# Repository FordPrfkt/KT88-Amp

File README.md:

# KT88-Amp
Tube Amplifier using KT88 Tubes

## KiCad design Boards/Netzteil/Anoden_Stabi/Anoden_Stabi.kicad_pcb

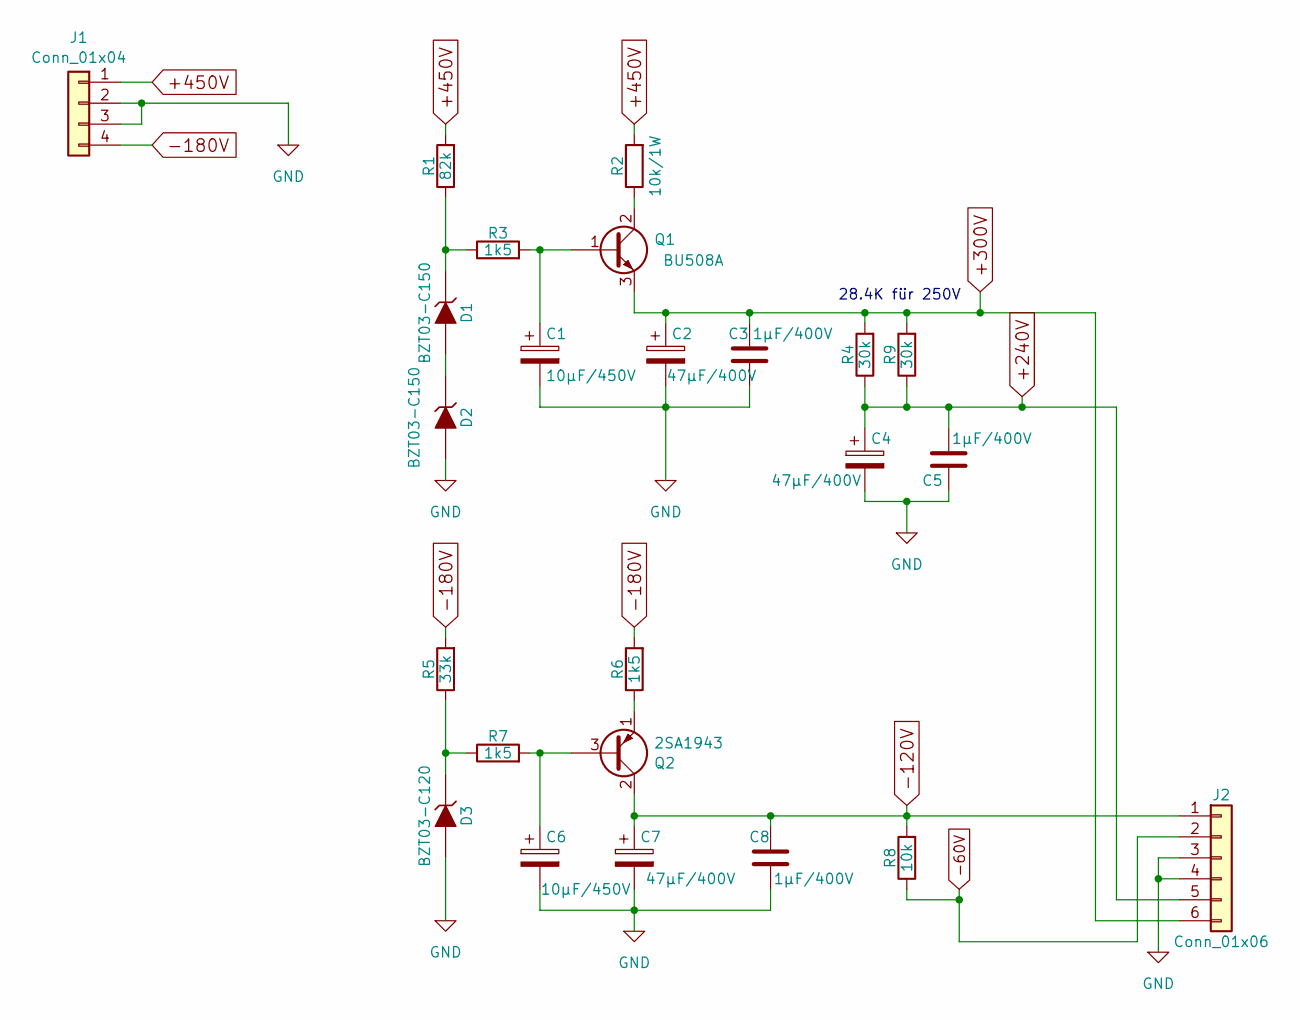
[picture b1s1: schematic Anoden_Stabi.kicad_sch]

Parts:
C1, C6: 10µF/450V; CP_Radial_D12.5mm_P5.00mm
C2, C4, C7: 47µF/400V; CP_Radial_D17.0mm_P7.50mm
C3, C5, C8: 1µF/400V; C_Rect_L31.5mm_W11.0mm_P27.50mm_MKS4
D1, D2: BZT03-C150; D_DO-41_SOD81_P10.16mm_Horizontal
D3: BZT03-C120; D_DO-41_SOD81_P10.16mm_Horizontal
J1: Conn_01x04; Molex_Mini-Fit_Jr_5566-04A_2x02_P4.20mm_Vertical
J2: Conn_01x06; Molex_Mini-Fit_Jr_5566-06A_2x03_P4.20mm_Vertical
Q1: BU508A; TO-3P-3_Vertical
Q2: 2SA1943; TO-3P-3_Vertical
R1: 82k; R_Axial_DIN0207_L6.3mm_D2.5mm_P10.16mm_Horizontal
R2: 10k/1W; R_Axial_DIN0414_L11.9mm_D4.5mm_P15.24mm_Horizontal
R3, R6, R7: 1k5; R_Axial_DIN0414_L11.9mm_D4.5mm_P15.24mm_Horizontal
R4, R9: 30k; R_Axial_DIN0207_L6.3mm_D2.5mm_P10.16mm_Horizontal
R5: 33k; R_Axial_DIN0207_L6.3mm_D2.5mm_P10.16mm_Horizontal
R8: 10k; R_Axial_DIN0414_L11.9mm_D4.5mm_P15.24mm_Horizontal

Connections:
+240V: C4.1, C5.2, J2.5, R4.1, R9.1
+300V: C2.1, C3.2, J2.6, Q1.3 (E), R4.2, R9.2
+450V: J1.1, R1.2, R2.2
-60V: J2.2, R8.1
-120V: C7.1, C8.2, J2.1, Q2.2 (C), R8.2
-180V: J1.4, R5.2, R6.2
GND: C1.2, C2.2, C3.1, C4.2, C5.1, C6.2, C7.2, C8.1, D2.2 (A), D3.2 (A), J1.2, J1.3, J2.3, J2.4
unnamed: D1.2 (A), D2.1 (K)
unnamed: D1.1 (K), R1.1, R3.1
unnamed: D3.1 (K), R5.1, R7.1
unnamed: C1.1, Q1.1 (B), R3.2
unnamed: Q1.2 (C), R2.1
unnamed: C6.1, Q2.3 (B), R7.2
unnamed: Q2.1 (E), R6.1

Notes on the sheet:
28.4K für 250V

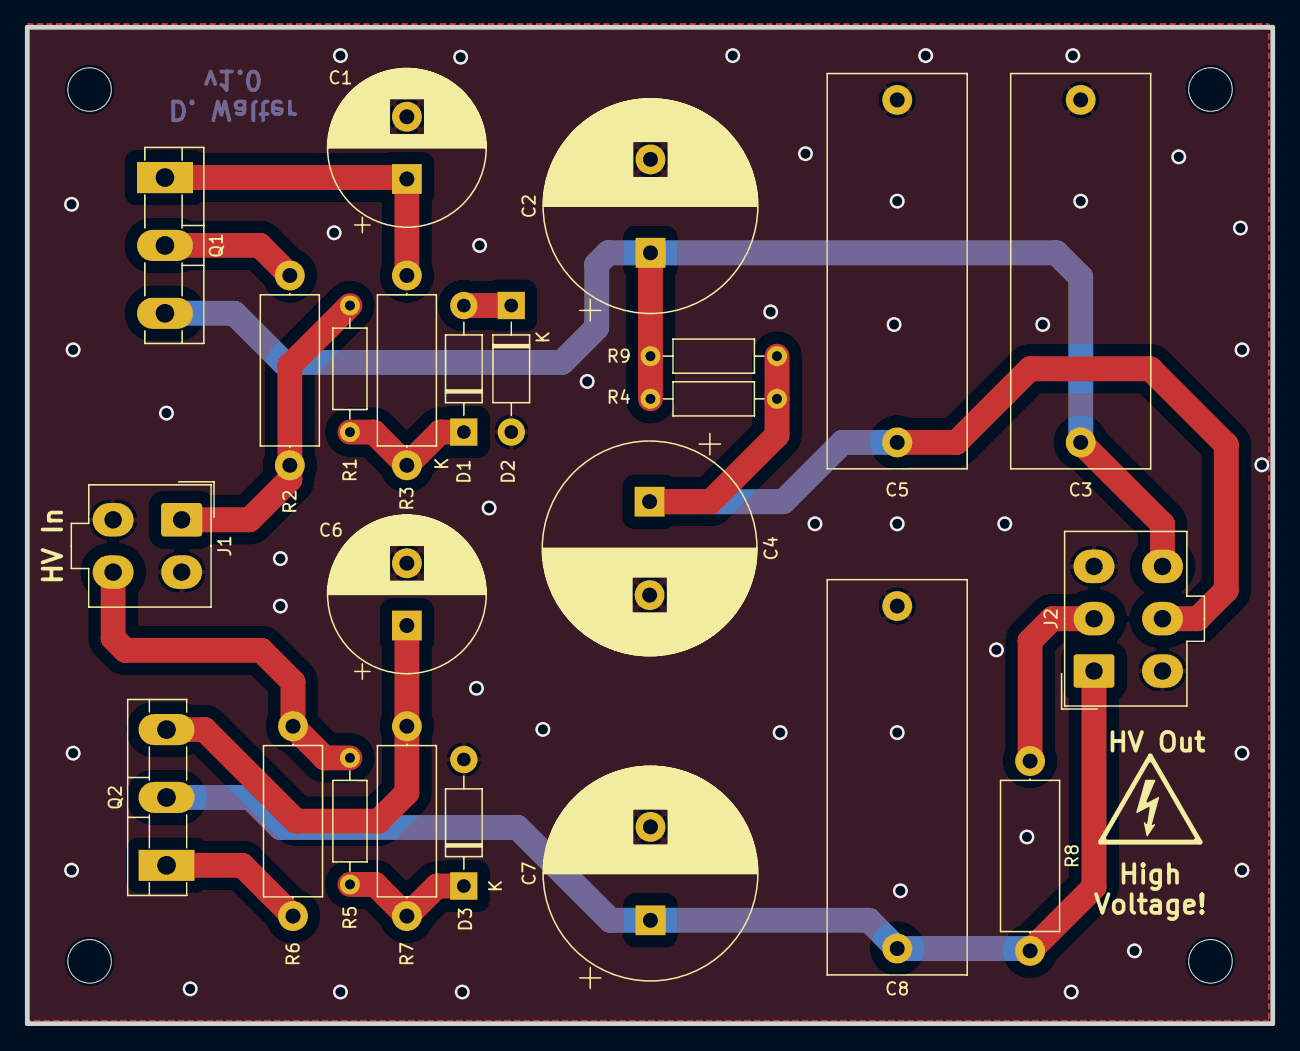
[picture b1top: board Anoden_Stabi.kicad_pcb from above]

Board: 2 copper layers, 100.0 x 80.0 mm, 24 parts (0 on the bottom side), 14 nets.

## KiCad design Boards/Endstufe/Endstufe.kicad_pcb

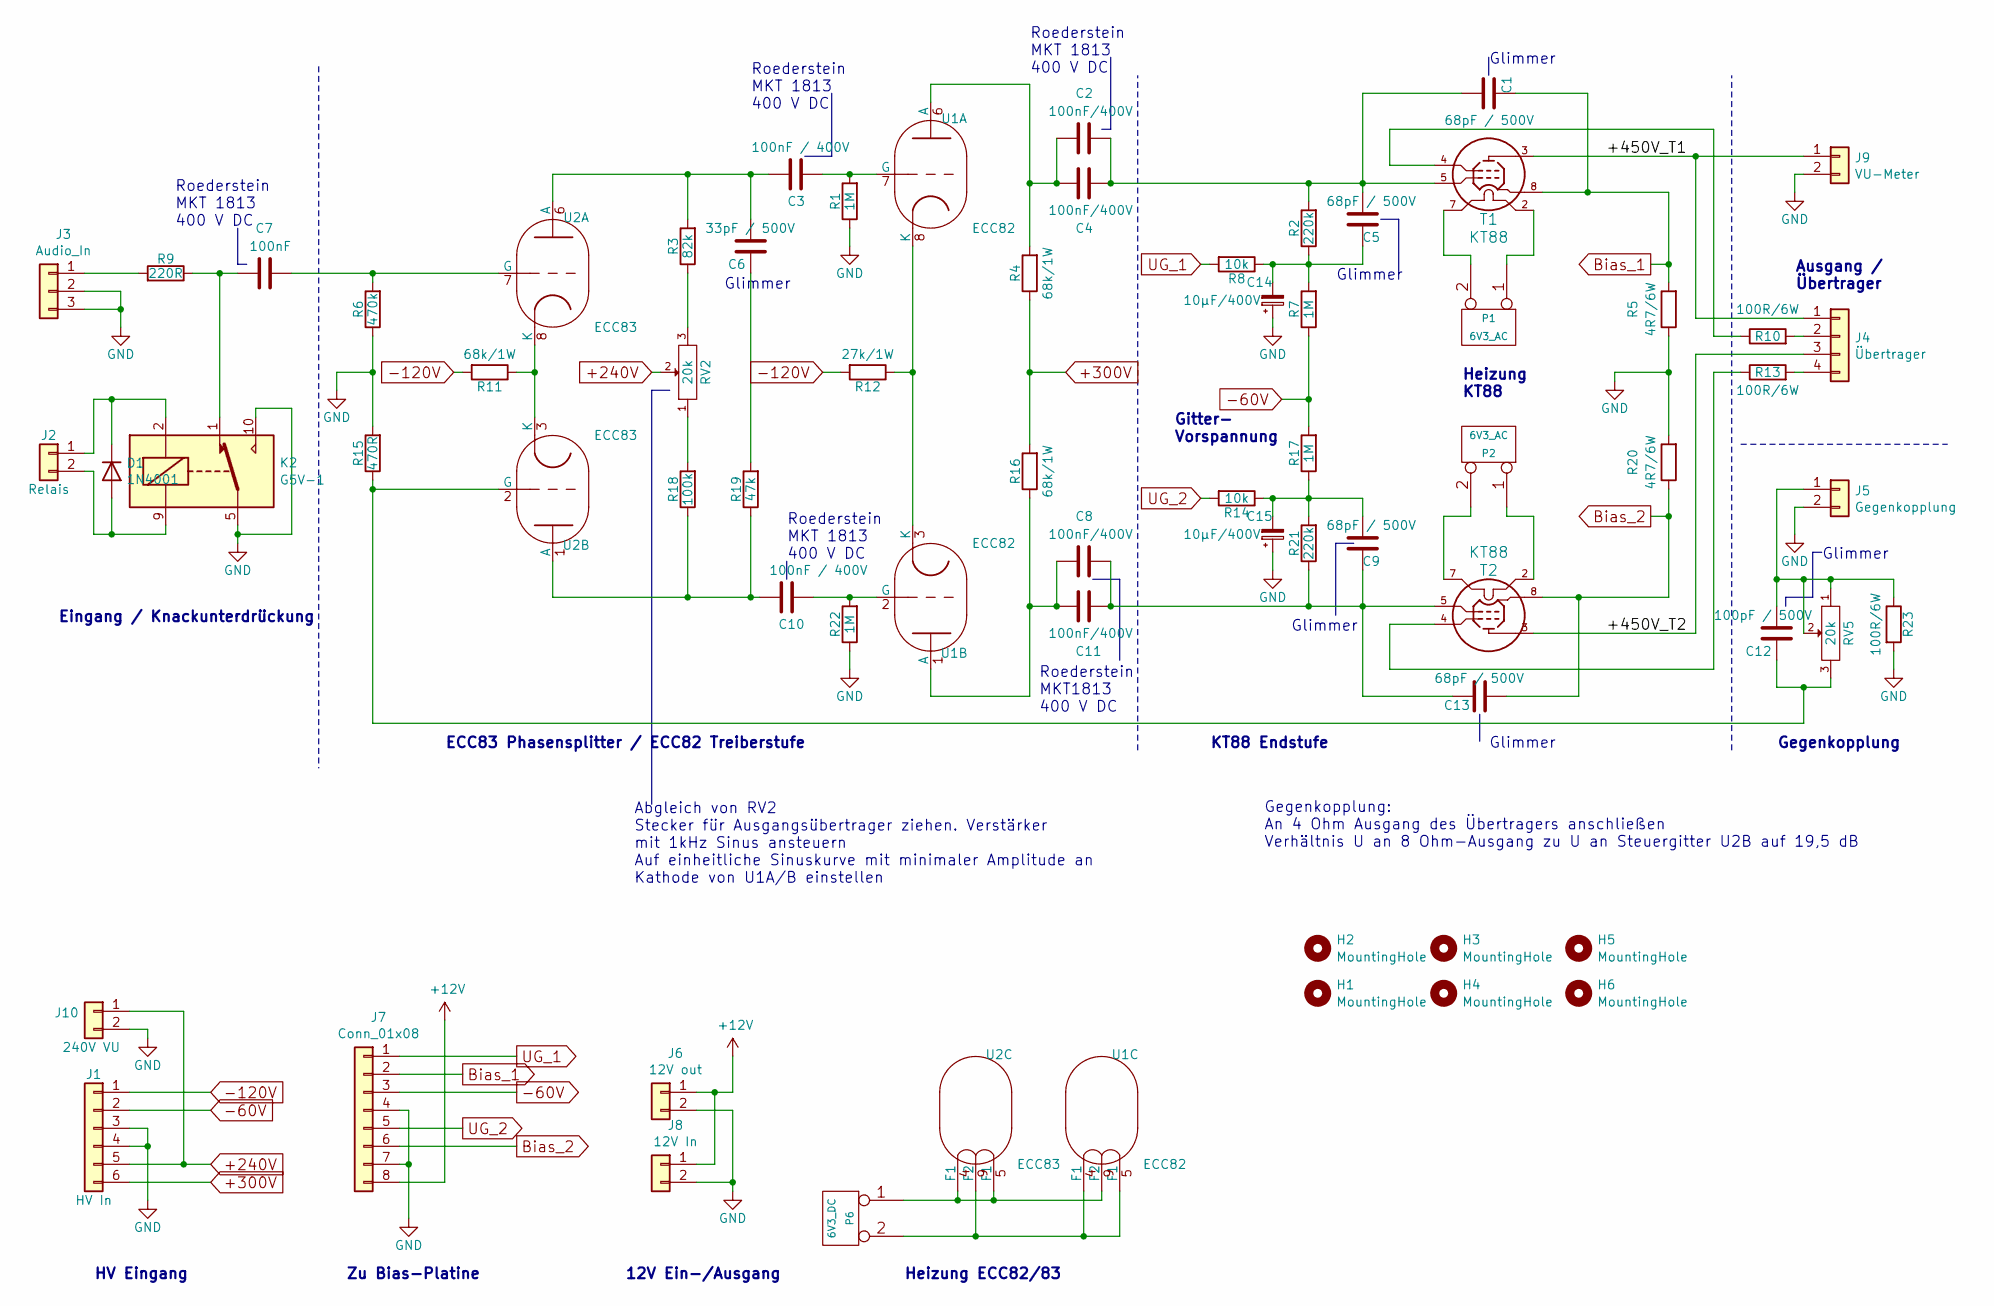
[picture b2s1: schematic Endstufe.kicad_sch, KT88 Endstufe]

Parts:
C1, C5, C9, C13: 68pF / 500V; C_Disc_D11.0mm_W5.0mm_P7.50mm
C2, C4, C8, C11: 100nF/400V; C_Axial_L19.0mm_D7.5mm_P25.00mm_Horizontal
C3, C10: 100nF / 400V; C_Axial_L19.0mm_D7.5mm_P25.00mm_Horizontal
C6: 33pF / 500V; C_Disc_D11.0mm_W5.0mm_P7.50mm
C7: 100nF; C_Axial_L19.0mm_D7.5mm_P25.00mm_Horizontal
C12: 100pF / 500V; C_Disc_D11.0mm_W5.0mm_P7.50mm
C14, C15: 10µF/400V; CP_Radial_D12.5mm_P5.00mm
D1: 1N4001; D_DO-41_SOD81_P10.16mm_Horizontal
H1, H2, H3, H4, H5, H6: MountingHole; MountingHole_3.2mm_M3
J1: HV In; Molex_Mini-Fit_Jr_5566-06A_2x03_P4.20mm_Vertical
J2: Relais; Molex_KK-254_AE-6410-02A_1x02_P2.54mm_Vertical
J3: Audio_In; JST_EH_B3B-EH-A_1x03_P2.50mm_Vertical
J4: Übertrager; Molex_Mini-Fit_Jr_5566-04A_2x02_P4.20mm_Vertical
J5: Gegenkopplung; Molex_Mini-Fit_Jr_5566-02A_2x01_P4.20mm_Vertical
J6: 12V out; Molex_KK-254_AE-6410-02A_1x02_P2.54mm_Vertical
J7: Conn_01x08; IDC-Header_2x04_P2.54mm_Vertical
J8: 12V In; Molex_KK-254_AE-6410-02A_1x02_P2.54mm_Vertical
J9: VU-Meter; Molex_Mini-Fit_Jr_5566-02A_2x01_P4.20mm_Vertical
J10: 240V VU; Molex_Mini-Fit_Jr_5566-02A_2x01_P4.20mm_Vertical
K2: G5V-1; Relay_SPDT_Omron_G5V-1
P1, P2: 6V3_AC; Molex_Mini-Fit_Jr_5566-02A_2x01_P4.20mm_Vertical
P6: 6V3_DC; Molex_Mini-Fit_Jr_5566-02A_2x01_P4.20mm_Vertical
R1, R7, R17, R22: 1M; R_Axial_DIN0207_L6.3mm_D2.5mm_P10.16mm_Horizontal
R2, R21: 220k; R_Axial_DIN0207_L6.3mm_D2.5mm_P10.16mm_Horizontal
R3: 82k; R_Axial_DIN0207_L6.3mm_D2.5mm_P10.16mm_Horizontal
R4, R16: 68k/1W; R_Axial_DIN0207_L6.3mm_D2.5mm_P10.16mm_Horizontal
R5, R20: 4R7/6W; R_Axial_DIN0922_L20.0mm_D9.0mm_P25.40mm_Horizontal
R6: 470k; R_Axial_DIN0207_L6.3mm_D2.5mm_P10.16mm_Horizontal
R8, R14: 10k; R_Axial_DIN0207_L6.3mm_D2.5mm_P10.16mm_Horizontal
R9: 220R; R_Axial_DIN0207_L6.3mm_D2.5mm_P10.16mm_Horizontal
R10, R13, R23: 100R/6W; R_Axial_DIN0922_L20.0mm_D9.0mm_P25.40mm_Horizontal
R11: 68k/1W; R_Axial_DIN0207_L6.3mm_D2.5mm_P15.24mm_Horizontal
R12: 27k/1W; R_Axial_DIN0207_L6.3mm_D2.5mm_P15.24mm_Horizontal
R15: 470R; R_Axial_DIN0207_L6.3mm_D2.5mm_P10.16mm_Horizontal
R18: 100k; R_Axial_DIN0207_L6.3mm_D2.5mm_P10.16mm_Horizontal
R19: 47k; R_Axial_DIN0207_L6.3mm_D2.5mm_P10.16mm_Horizontal
RV2, RV5: 20k; Potentiometer_Vishay_T7-YA_Single_Vertical
T1, T2: KT88; Valve_Octal
U1: ECC82; Valve_ECC-83-1
U2: ECC83; Valve_ECC-83-1

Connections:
+12V: J6.1, J7.8, J8.1
+240V: J1.5, J10.1, RV2.2
+300V: J1.6, R4.1, R16.2
-60V: J1.2, J7.3, R7.1, R17.2
-120V: J1.1, R11.2, R12.2
/+450V_T1: J4.1, J9.1, T1.3 (a)
/+450V_T2: J4.3, T2.3 (a)
Bias_1: C1.1, J7.2, R5.2, T1.8 (k)
Bias_2: C13.2, J7.6, R20.1, T2.8 (k)
GND: C14.1, C15.1, J1.3, J1.4, J3.2, J3.3, J5.2, J6.2, J7.4, J7.7, J8.2, J9.2, J10.2, K2.5, K2.6, K2.10, R1.1, R5.1, R6.1, R15.2, R20.2, R22.1, R23.2
unnamed: C6.1, R19.2
unnamed: C7.1, K2.1, R9.1
unnamed: C5.1, C14.2, R2.1, R7.2, R8.1
unnamed: C9.2, C15.2, R14.1, R17.1, R21.2
unnamed: D1.2 (A), J2.2, K2.9
unnamed: D1.1 (K), J2.1, K2.2
unnamed: J3.1, R9.2
unnamed: J4.2, R10.2
unnamed: J4.4, R13.2
unnamed: C12.2, J5.1, R23.1, RV5.1, RV5.2
unnamed: P1.1, T1.2 (f)
unnamed: P1.2, T1.7 (f)
unnamed: P2.1, T2.2 (f)
unnamed: P2.2, T2.7 (f)
unnamed: P6.1, U1.9 (F2), U2.4 (F1), U2.5 (F1)
unnamed: P6.2, U1.4 (F1), U1.5 (F1), U2.9 (F2)
unnamed: R3.1, RV2.3
unnamed: R18.2, RV2.1
unnamed: C1.2, C2.1, C4.1, C5.2, R2.2, T1.5 (g1)
unnamed: R10.1, T1.4 (g2)
unnamed: C8.1, C9.1, C11.1, C13.1, R21.1, T2.5 (g1)
unnamed: R13.1, T2.4 (g2)
unnamed: C2.2, C4.2, R4.2, U1.6 (A)
unnamed: C3.1, R1.2, U1.7 (G)
unnamed: R12.1, U1.3 (K), U1.8 (K)
unnamed: C8.2, C11.2, R16.1, U1.1 (A)
unnamed: C10.1, R22.2, U1.2 (G)
unnamed: C3.2, C6.2, R3.2, U2.6 (A)
unnamed: C7.2, R6.2, U2.7 (G)
unnamed: R11.1, U2.3 (K), U2.8 (K)
unnamed: C10.2, R18.1, R19.1, U2.1 (A)
unnamed: C12.1, R15.1, RV5.3, U2.2 (G)
UG_1: J7.1, R8.2
UG_2: J7.5, R14.2

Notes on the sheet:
Glimmer
Heizung ECC82/83
Gitter- Vorspannung
Abgleich von RV2 Stecker für Ausgangsübertrager ziehen. Verstärker mit 1kHz Sinus ansteuern Auf einheitliche Sinuskurve mit minimaler Amplitude an Kathode von U1A/B einstellen
HV Eingang
Ausgang / Übertrager
Eingang / Knackunterdrückung
12V Ein-/Ausgang
Gegenkopplung: An 4 Ohm Ausgang des Übertragers anschließen Verhältnis U an 8 Ohm-Ausgang zu U an Steuergitter U2B auf 19,5 dB
Roederstein MKT 1813 400 V DC
Zu Bias-Platine
Gegenkopplung
ECC83 Phasensplitter / ECC82 Treiberstufe
KT88 Endstufe
Roederstein MKT1813 400 V DC
Roederstein MKT 1813 400 V DC
Heizung KT88

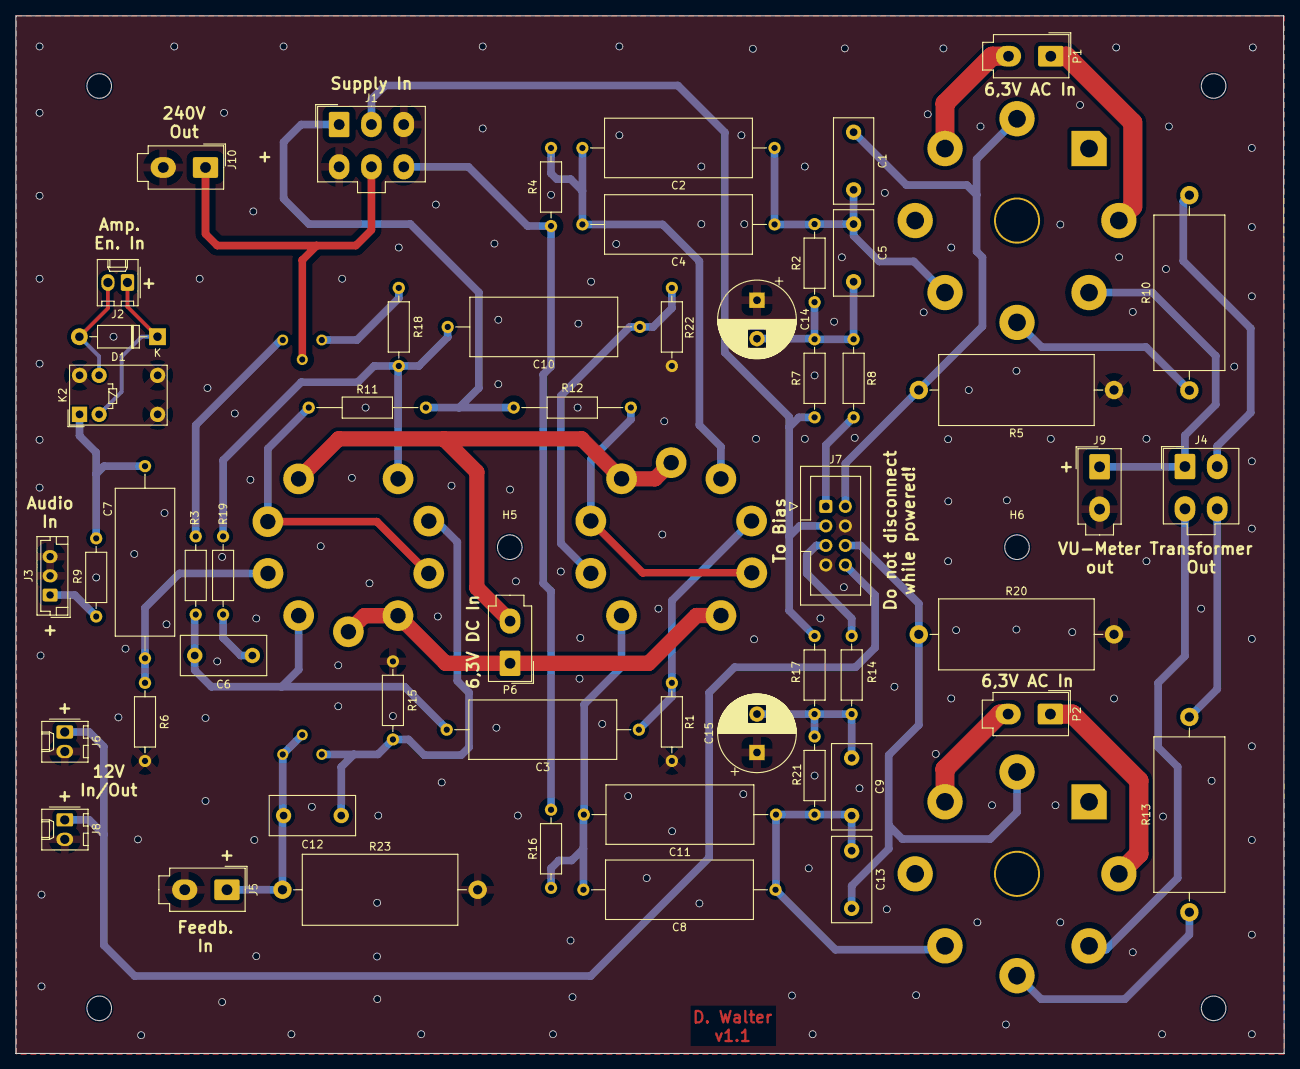
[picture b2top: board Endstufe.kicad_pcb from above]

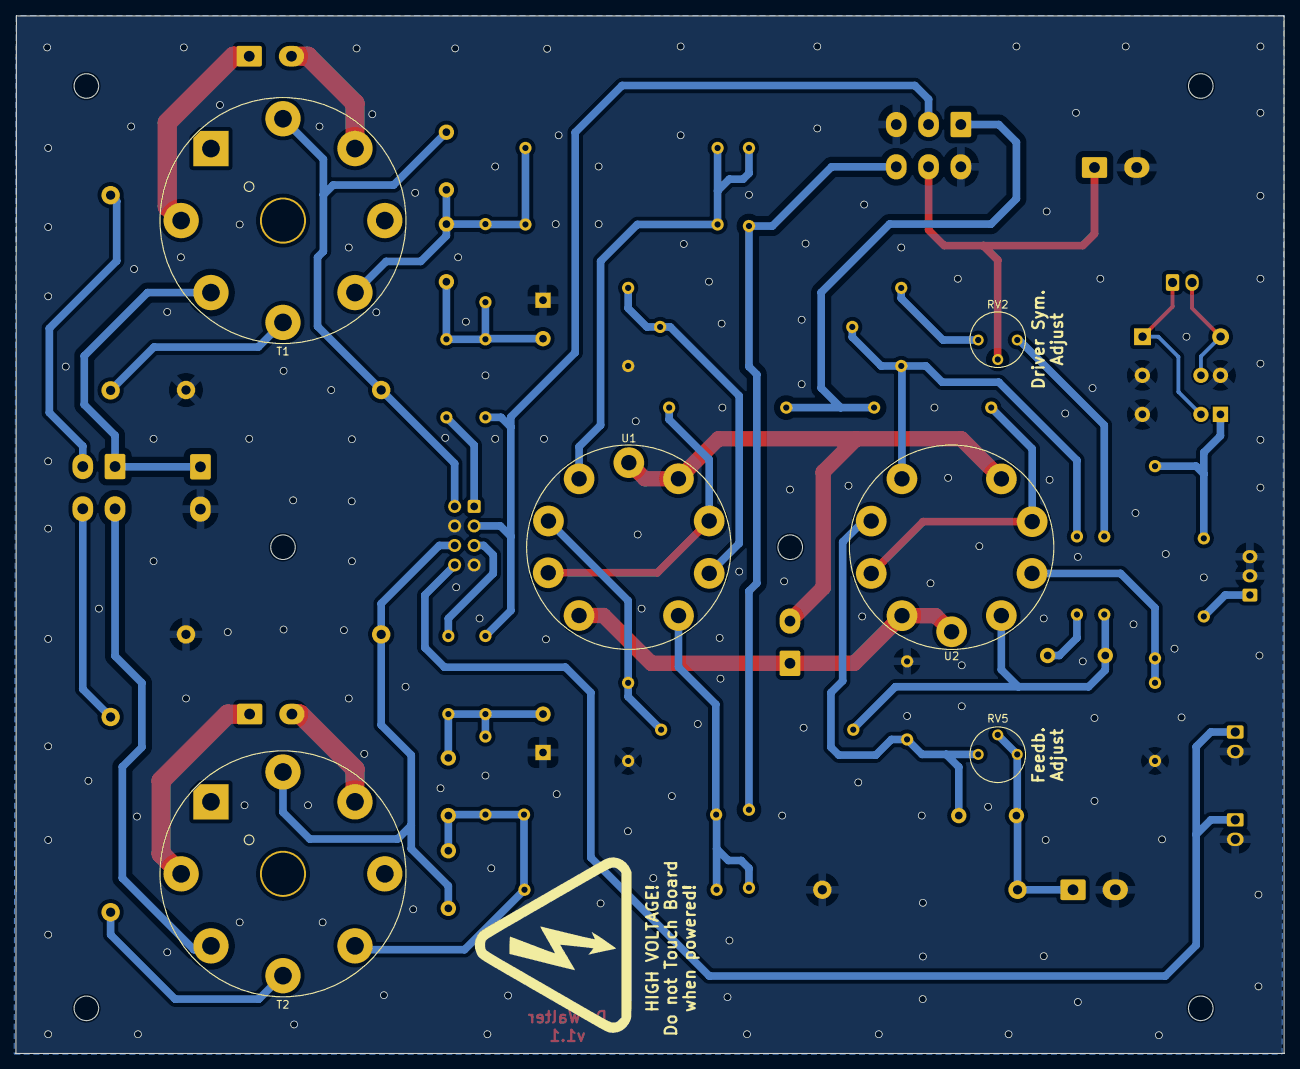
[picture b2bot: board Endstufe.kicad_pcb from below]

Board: 2 copper layers, 165.0 x 135.0 mm, 65 parts (6 on the bottom side), 44 nets.

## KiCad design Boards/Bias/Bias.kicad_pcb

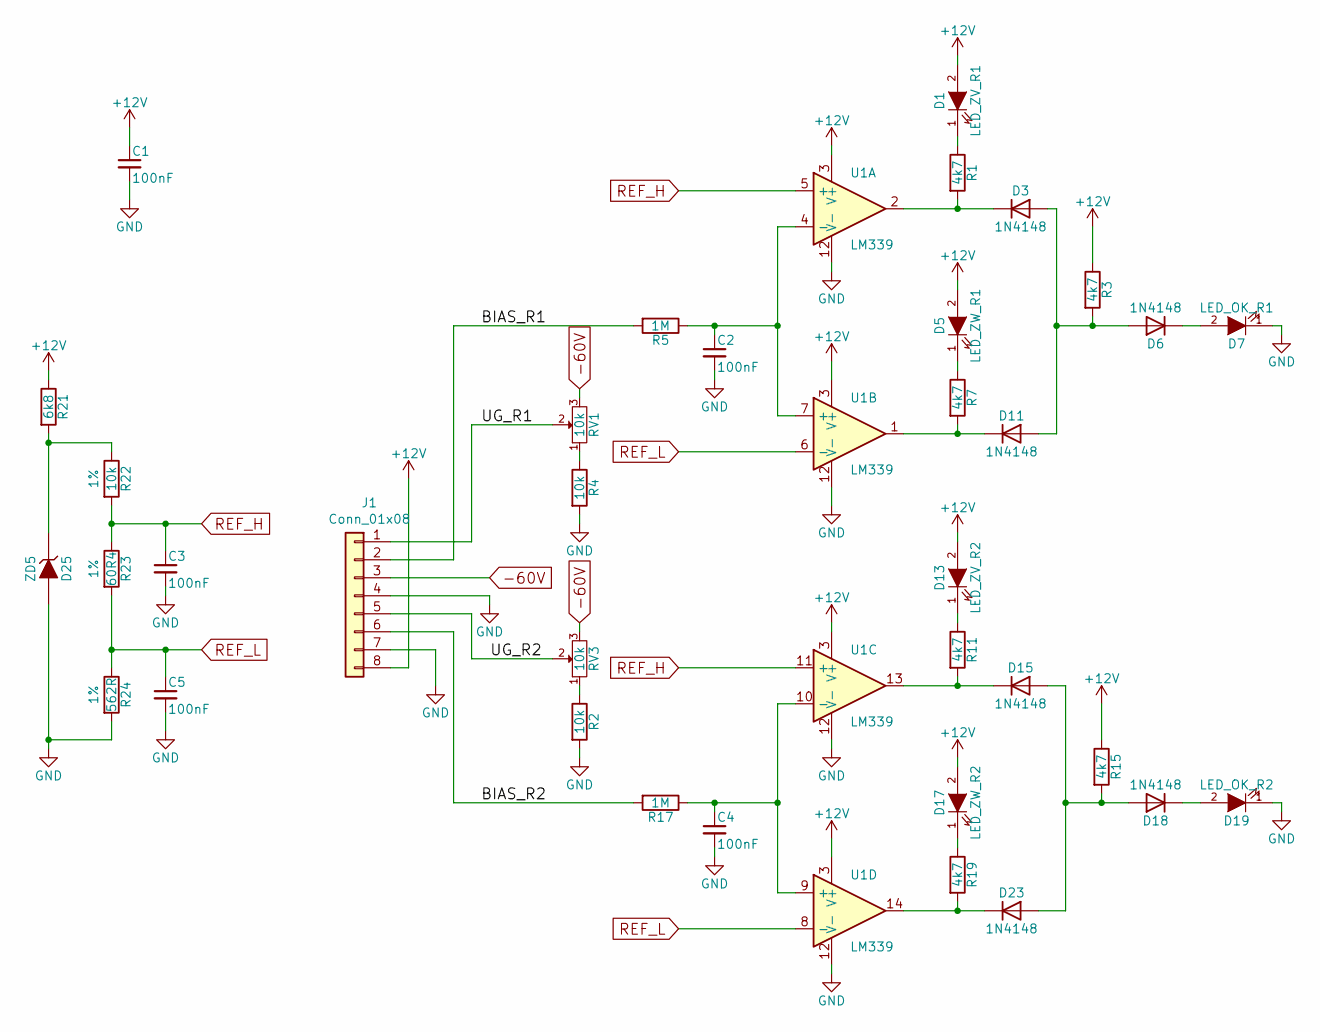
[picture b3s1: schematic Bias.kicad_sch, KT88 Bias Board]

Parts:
C1, C2, C3, C4, C5: 100nF; C_Disc_D4.3mm_W1.9mm_P5.00mm
D1: LED_ZV_R1; LED_D3.0mm
D3, D6, D11, D15, D18, D23: 1N4148; D_DO-35_SOD27_P10.16mm_Horizontal
D5: LED_ZW_R1; LED_D3.0mm
D7: LED_OK_R1; LED_D3.0mm
D13: LED_ZV_R2; LED_D3.0mm
D17: LED_ZW_R2; LED_D3.0mm
D19: LED_OK_R2; LED_D3.0mm
D25: ZD5; D_DO-41_SOD81_P10.16mm_Horizontal
J1: Conn_01x08; IDC-Header_2x04_P2.54mm_Vertical
R1, R3, R7, R11, R15, R19: 4k7; R_Axial_DIN0207_L6.3mm_D2.5mm_P10.16mm_Horizontal
R2, R4: 10k; R_Axial_DIN0207_L6.3mm_D2.5mm_P10.16mm_Horizontal
R5, R17: 1M; R_Axial_DIN0207_L6.3mm_D2.5mm_P10.16mm_Horizontal
R21: 6k8; R_Axial_DIN0207_L6.3mm_D2.5mm_P10.16mm_Horizontal
R22: 10k; R_Axial_DIN0207_L6.3mm_D2.5mm_P10.16mm_Horizontal; Tolerance 1%
R23: 60R4; R_Axial_DIN0207_L6.3mm_D2.5mm_P10.16mm_Horizontal; Tolerance 1%
R24: 562R; R_Axial_DIN0207_L6.3mm_D2.5mm_P10.16mm_Horizontal; Tolerance 1%
RV1, RV3: 10k; Potentiometer_Piher_PT-10-V10_Vertical_Hole
U1: LM339; DIP-14_W7.62mm

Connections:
+12V: C1.1, D1.2 (A), D5.2 (A), D13.2 (A), D17.2 (A), J1.8, R3.1, R15.1, R21.1, U1.3 (V+)
-60V: J1.3, RV1.3, RV3.3
/BIAS_R1: J1.2, R5.2
/BIAS_R2: J1.6, R17.2
/UG_R1: J1.1, RV1.2
/UG_R2: J1.5, RV3.2
GND: C1.2, C2.2, C3.2, C4.2, C5.2, D7.1 (K), D19.1 (K), D25.2 (A), J1.4, J1.7, R2.2, R4.2, R24.2, U1.12 (V-)
unnamed: D1.1 (K), R1.1
unnamed: D3.1 (K), R1.2, U1.2
unnamed: D5.1 (K), R7.1
unnamed: D6.1 (K), D7.2 (A)
unnamed: D3.2 (A), D6.2 (A), D11.2 (A), R3.2
unnamed: D11.1 (K), R7.2, U1.1
unnamed: D13.1 (K), R11.1
unnamed: D15.2 (A), D18.2 (A), D23.2 (A), R15.2
unnamed: D15.1 (K), R11.2, U1.13
unnamed: D17.1 (K), R19.1
unnamed: D18.1 (K), D19.2 (A)
unnamed: D23.1 (K), R19.2, U1.14
unnamed: D25.1 (K), R21.2, R22.1
unnamed: R2.1, RV3.1
unnamed: R4.1, RV1.1
unnamed: C2.1, R5.1, U1.4 (-), U1.7 (+)
unnamed: C4.1, R17.1, U1.9 (+), U1.10 (-)
REF_H: C3.1, R22.2, R23.1, U1.5 (+), U1.11 (+)
REF_L: C5.1, R23.2, R24.1, U1.6 (-), U1.8 (-)

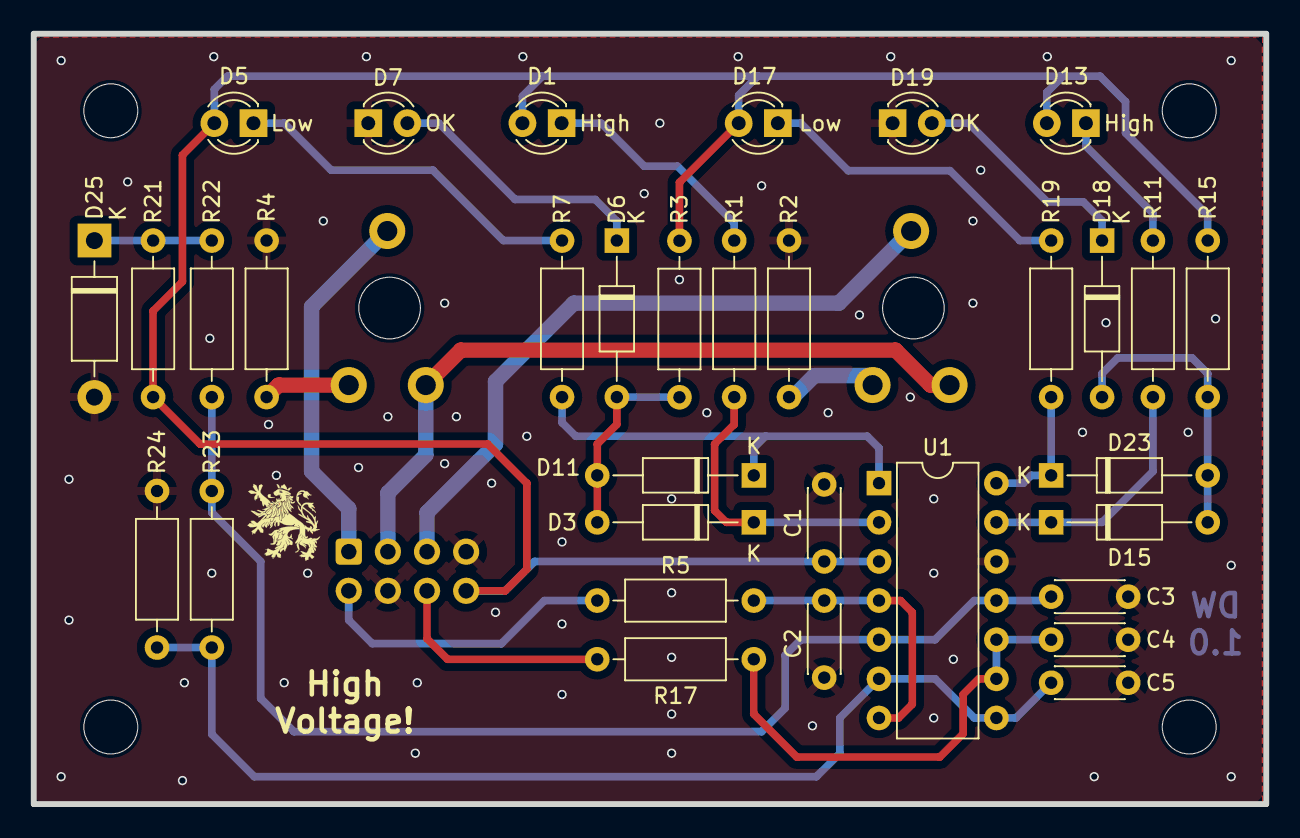
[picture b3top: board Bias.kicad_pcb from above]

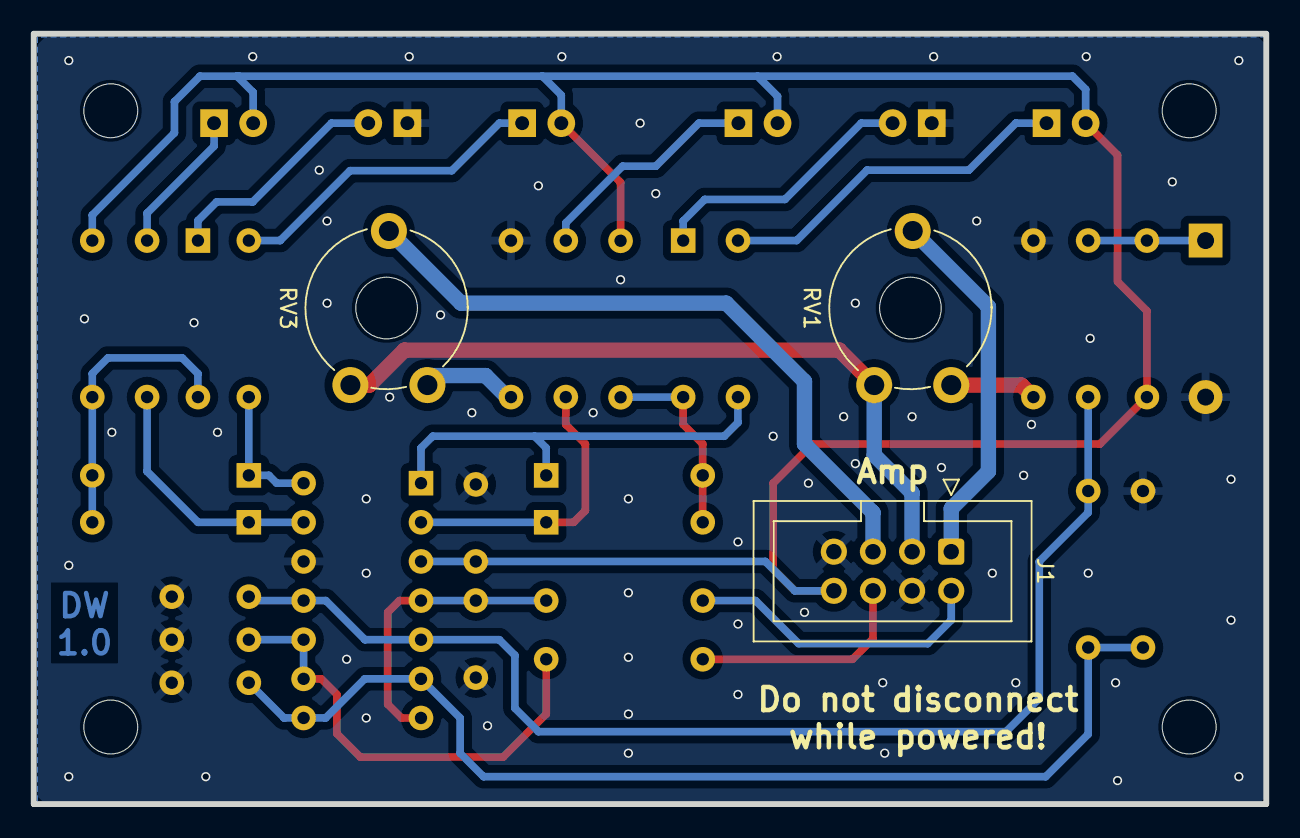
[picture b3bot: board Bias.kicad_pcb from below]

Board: 2 copper layers, 80.0 x 50.0 mm, 36 parts (3 on the bottom side), 26 nets.

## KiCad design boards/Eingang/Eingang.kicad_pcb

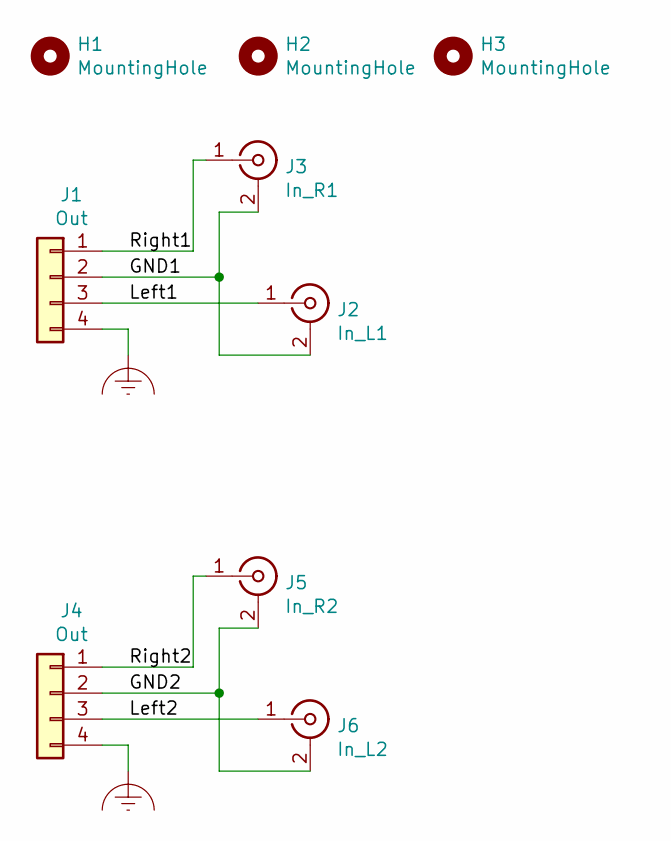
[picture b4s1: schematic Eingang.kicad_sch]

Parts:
H1, H2, H3: MountingHole; MountingHole_3.2mm_M3
J1, J4: Out; JST_EH_B4B-EH-A_1x04_P2.50mm_Vertical
J2: In_L1; BTOR1
J3: In_R1; BTOR1
J5: In_R2; BTOR1
J6: In_L2; BTOR1

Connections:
/GND1: J1.2, J2.2 (Ext), J3.2 (Ext)
/GND2: J4.2, J5.2 (Ext), J6.2 (Ext)
/Left1: J1.3, J2.1 (In)
/Left2: J4.3, J6.1 (In)
/Right1: J1.1, J3.1 (In)
/Right2: J4.1, J5.1 (In)
Earth_Clean: J1.4, J4.4

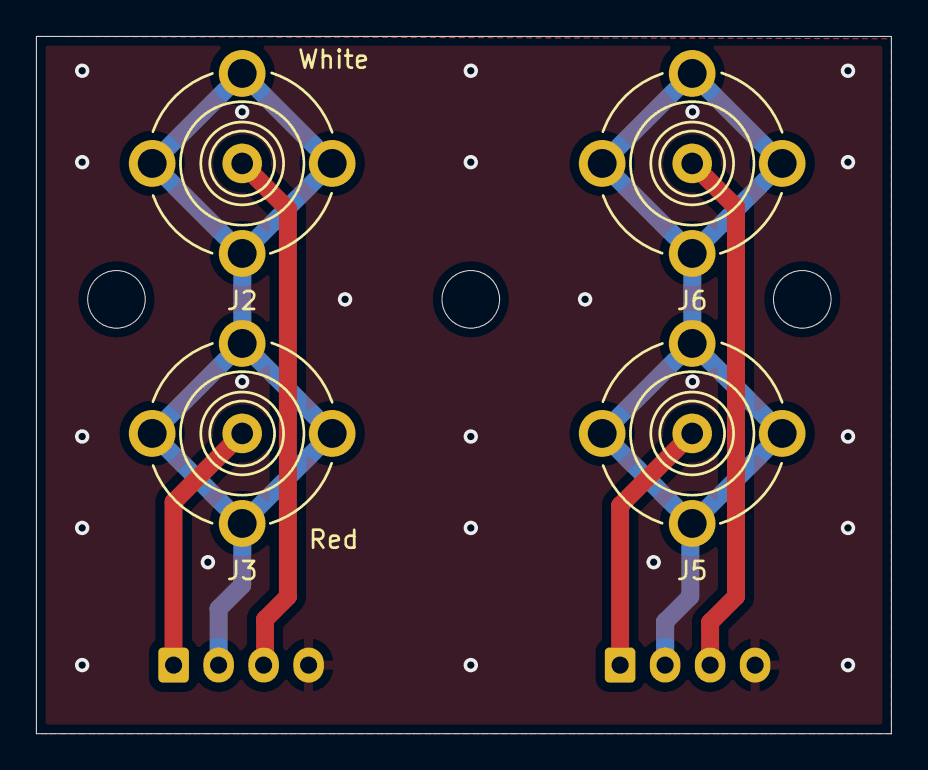
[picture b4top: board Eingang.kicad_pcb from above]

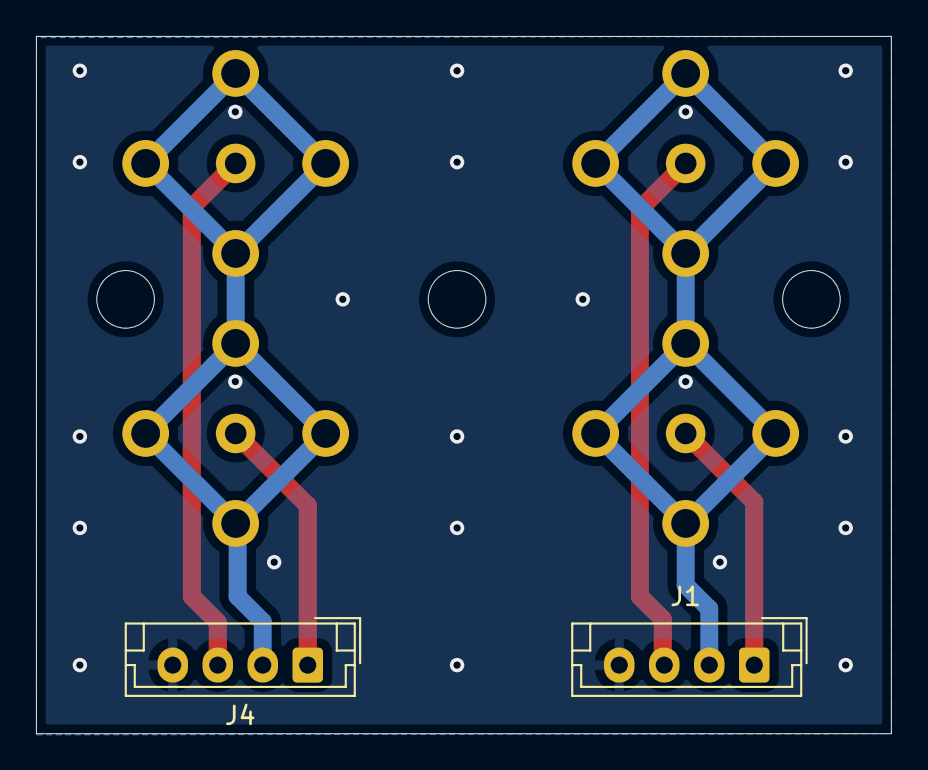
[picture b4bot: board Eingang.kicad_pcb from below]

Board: 2 copper layers, 47.5 x 38.7 mm, 9 parts (2 on the bottom side), 7 nets.

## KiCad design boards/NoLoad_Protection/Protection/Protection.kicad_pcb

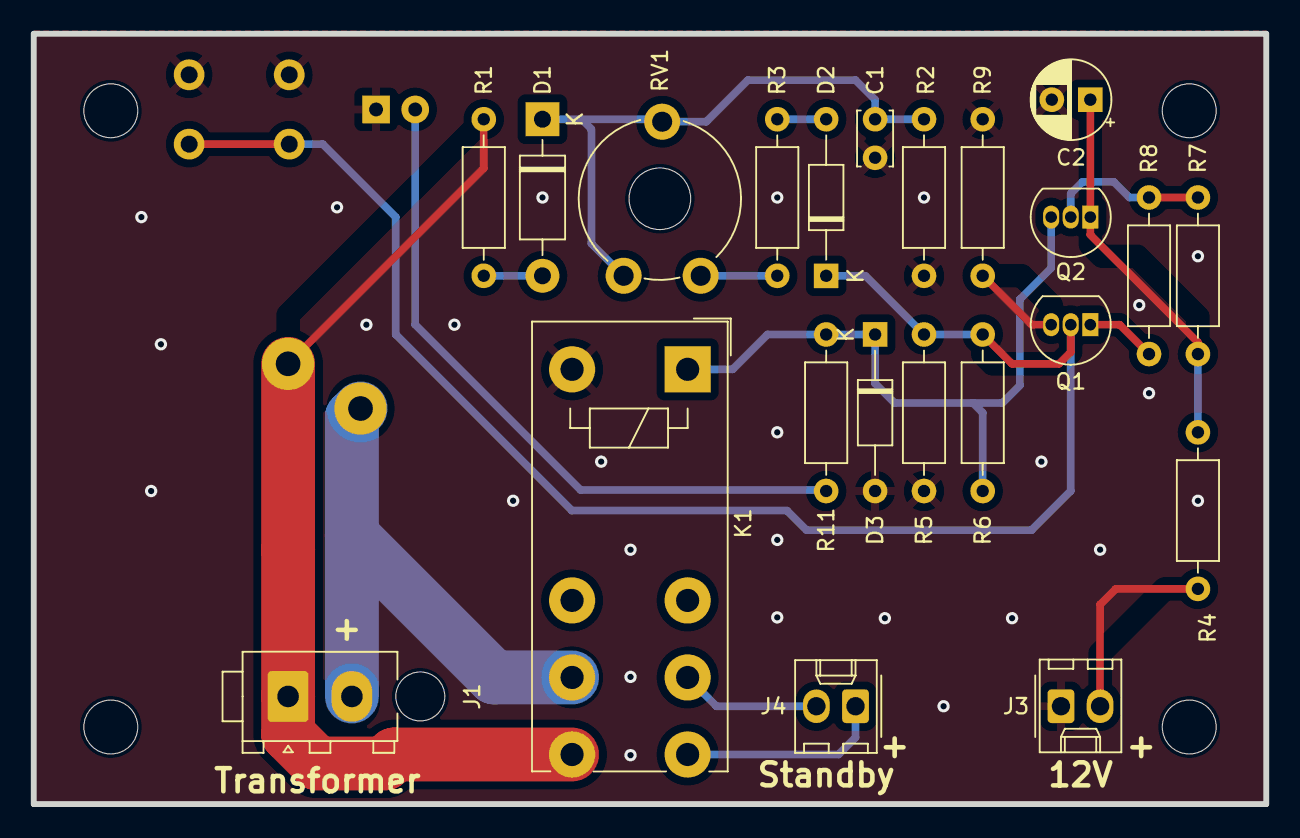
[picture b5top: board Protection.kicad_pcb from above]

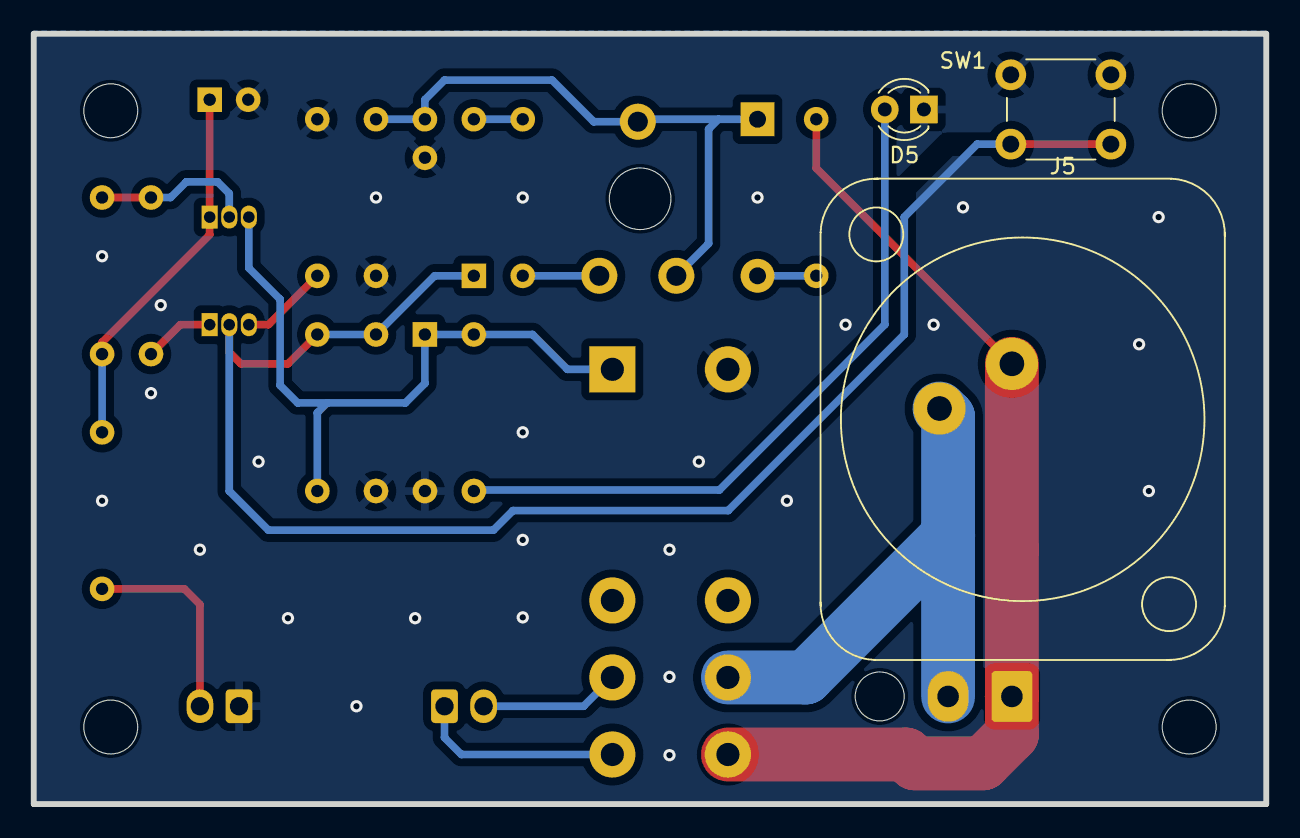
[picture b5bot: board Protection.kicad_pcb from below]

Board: 2 copper layers, 80.0 x 50.0 mm, 25 parts (3 on the bottom side), 17 nets.

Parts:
C1: 47nF; C_Disc_D3.4mm_W2.1mm_P2.50mm
C2: 47µF; CP_Radial_D5.0mm_P2.50mm
D1: 1N4007; D_DO-41_SOD81_P10.16mm_Horizontal
D2, D3: 1N4148; D_DO-35_SOD27_P10.16mm_Horizontal
D5: LED; LED_D3.0mm
J1: Transformer; TE_MATE-N-LOK_1-770866-x_1x02_P4.14mm_Vertical
J3: 12V_In; Molex_KK-254_AE-6410-02A_1x02_P2.54mm_Vertical
J4: Standby; Molex_KK-254_AE-6410-02A_1x02_P2.54mm_Vertical
J5: Speaker; Jack_speakON_Neutrik_NL2MD-V_Vertical
K1: FINDER-40.52; Relay_DPDT_Finder_40.52
Q1: BC546; TO-92_Inline
Q2: BC327; TO-92_Inline
R1: 1k5; R_Axial_DIN0207_L6.3mm_D2.5mm_P10.16mm_Horizontal
R2: 47k; R_Axial_DIN0207_L6.3mm_D2.5mm_P10.16mm_Horizontal
R3: 10k; R_Axial_DIN0207_L6.3mm_D2.5mm_P10.16mm_Horizontal
R4: 10R; R_Axial_DIN0207_L6.3mm_D2.5mm_P10.16mm_Horizontal
R5: 3k3; R_Axial_DIN0207_L6.3mm_D2.5mm_P10.16mm_Horizontal
R6: 33k; R_Axial_DIN0207_L6.3mm_D2.5mm_P10.16mm_Horizontal
R7: 1k; R_Axial_DIN0207_L6.3mm_D2.5mm_P10.16mm_Horizontal
R8: 4k7; R_Axial_DIN0207_L6.3mm_D2.5mm_P10.16mm_Horizontal
R9: 100R; R_Axial_DIN0207_L6.3mm_D2.5mm_P10.16mm_Horizontal
R11: R; R_Axial_DIN0207_L6.3mm_D2.5mm_P10.16mm_Horizontal
RV1: 250k; Potentiometer_Piher_PT-10-V10_Vertical_Hole
SW1: Reset; SW_PUSH_6mm_H7.3mm

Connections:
+12V: J3.2, R4.2
/Standby: J4.1, K1.14
GND: C1.2, C2.2, D3.2 (A), D5.1 (K), J3.1, K1.A2, R2.1, R5.1, R9.1, SW1.1
unnamed: D1.2 (A), R1.1
unnamed: C1.1, D1.1 (K), R2.2, RV1.2, RV1.3
unnamed: D2.2 (A), R3.1
unnamed: D2.1 (K), Q1.2 (B), R5.2, R6.2, SW1.2
unnamed: D3.1 (K), K1.A1, Q2.3 (E), R6.1, R11.2
unnamed: D5.2 (A), R11.1
unnamed: J1.1, J5.1+, K1.24, R1.2
unnamed: J1.2, J5.1-, K1.21
unnamed: J4.2, K1.11
unnamed: Q1.1 (C), R8.1
unnamed: Q1.3 (E), R9.2
unnamed: Q2.2 (B), R7.1, R8.2
unnamed: C2.1, Q2.1 (C), R4.1, R7.2
unnamed: R3.2, RV1.1
